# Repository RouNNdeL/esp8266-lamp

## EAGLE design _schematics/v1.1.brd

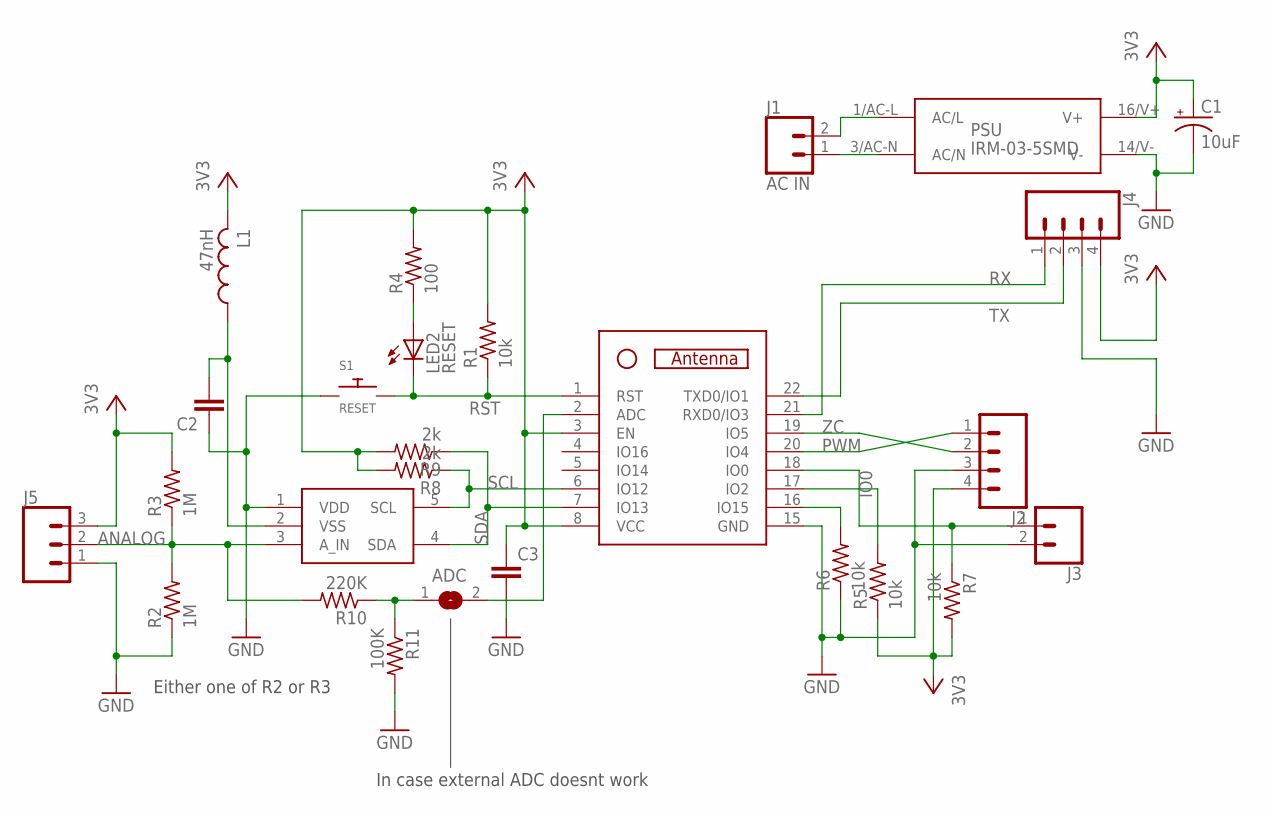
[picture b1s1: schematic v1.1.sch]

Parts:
ADC: SJ
C1: 10uF; 153CLV-0405
C2, C3: C-EUC0805; C0805
J1: AC IN; 1X2_5MM_SCREW
J2, J4: CONN_04; 1X04
J3: CONN_02; 1X02
J5: CONN_03; 1X03
L1: 47nH; L2012C
LED2: RESET; SML0805
PSU: IRM-03-5SMD; IRM-03-5S
R1, R5, R6, R7: 10k; R0603
R2, R3: 1M; R0603
R4: 100; R0805
R8, R9: 2k; R0603
R10: 220K; R0603
R11: 100K; R0603
S1: RESET; TACTILE_SWITCH_SMD_6.2MM_TALL
U1: ESP-07
U2: MCP3221; SOT23-5

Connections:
AC/L: J1.2, PSU.1/AC-L (AC/L)
AC/N: J1.1, PSU.3/AC-N (AC/N)
ANALOG: J5.2, R2.2, R3.1, R10.2, U2.3 (A_IN)
GND: C1.-, C2.1, C3.2, J2.3, J3.2, J4.3, J5.1, PSU.14/V- (V-), R2.1, R6.1, R11.2, S1.A1, S1.A2, U1.15 (GND), U2.1 (VDD)
IO0: J3.1, R7.1, U1.18 (IO0)
unnamed: LED2.A, R4.1
unnamed: R5.2, U1.17 (IO2)
unnamed: R6.2, U1.16 (IO15)
unnamed: ADC.1, R10.1, R11.1
unnamed: ADC.2, U1.2 (ADC)
unnamed: C2.2, L1.1, U2.2 (VSS)
PWM: J2.1, U1.20 (IO4)
RST: LED2.C, R1.1, S1.B1, S1.B2, U1.1 (RST)
RX: J4.1, U1.21 (RXD0/IO3)
SCL: R8.1, U1.6 (IO12), U2.5 (SCL)
SDA: R9.1, U1.7 (IO13), U2.4 (SDA)
TX: J4.2, U1.22 (TXD0/IO1)
VCC: C1.+, C3.1, J2.4, J4.4, J5.3, L1.2, PSU.16/V+ (V+), R1.2, R3.2, R4.2, R5.1, R7.2, R8.2, R9.2, U1.3 (EN), U1.8 (VCC)
ZC: J2.2, U1.19 (IO5)

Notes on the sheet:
Either one of R2 or R3
In case external ADC doesnt work

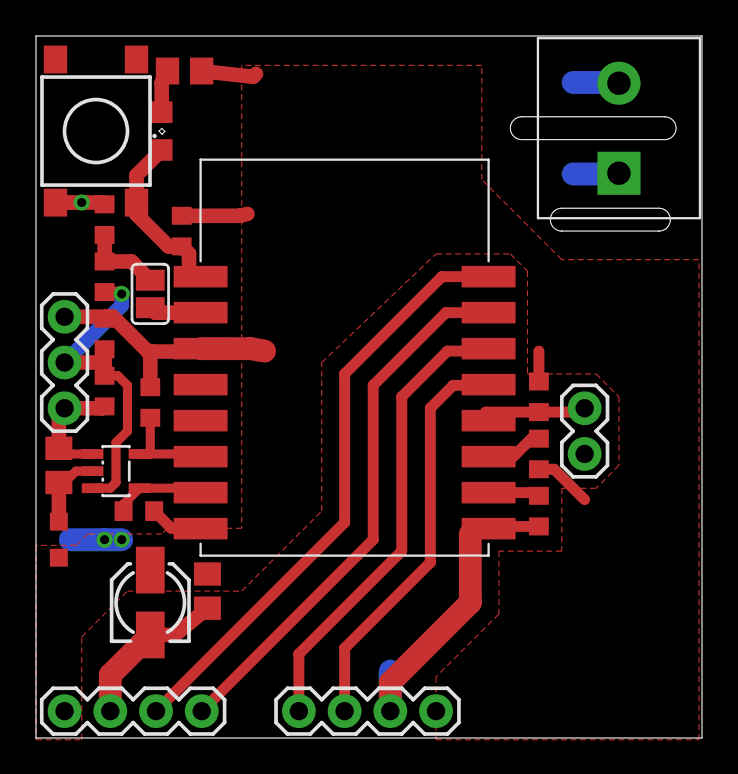
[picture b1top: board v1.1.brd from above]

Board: 2 copper layers, 37.0 x 39.0 mm, 26 parts (1 on the bottom side), 19 nets.

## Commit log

2018-05-13 Create LICENSE
2018-05-23 Update schematics
2018-06-09 [Schematics] Version 1.1 - Fix ADC polarity - Add input protection on programming header - Add voltage divider for RX signal
2018-12-18 Add C Code
2018-12-21 Fix TRIAC getting stuck by turning it of after it latches
2018-12-21 Improve brightness value locking and unlocking
2018-12-22 Add brightness polling (Driver polls WiFi)
2018-12-22 Send the last brightness on boot
2018-12-22 Change to TCP server. Remove EEPROM (caused crashes). Add state report
2018-12-22 Add a master register call on boot
2018-12-23 Fix TCP response sending
2018-12-23 Adjust ADC value for potentiometer
2018-12-23 Fix ADC error calculations
2018-12-23 Implement user interaction tracking and lock the ADC after it finishes
2019-06-24 Rewrite WiFi driver from scratch, more customization for dimming
2019-06-24 Bump version
2019-07-07 Add UDP local control protocol support
2019-07-07 Improve UDP performance by reporting state after a delay
2019-08-24 Fix packets not being received properly
2021-01-19 Version 2 - MQTT with Home Assistant

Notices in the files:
_schematics/v1.1.brd:
© 2018 Krzysztof Zdulski
parts and their libraries:
SparkFun-Connectors: Licensing: Creative Commons ShareAlike 4.0 International - https://creativecommons.org/licenses/by-sa/4.0
